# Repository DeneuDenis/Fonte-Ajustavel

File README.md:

# Fonte-Ajustavel
### Objetivo: montar uma fonte de tensão ajustável entre 12V e 3V que funcione com uma corrente de saída de 100 mA.
# Componentes
Todos os preços foram conferidos no site https://www.baudaeletronica.com.br
| Componente  |  Preço  |
| ------------------- | ------------------- |
|  Capacitor Eletrolítico 470uF / 35V |  R$ 0,77 |
|  Resistor 2K7 5% (1/4W) |  R$ 0,05 |
|  Resistor 1K8 5% (1/4W) |  R$ 0,05 |
|  Ponte Retificadora KBPC1010 |  R$ 3,67 |
|  Diodo Zener 1N4743 [13V / 1W] |  R$ 0,19 |
|  Potenciômetro Linear de 5K (5000Ω) |  R$ 1,99 |
|  Transistor NPN BC337 |  R$ 0,20 |
|  Transformador Trafo 12V+12V 500mA - 110/220VAC |  R$ 32,86 |
Vídeo curto com explicação dos valores escolhidos: https://drive.google.com/file/d/1bg3l0aVqp5aAvlKfoLDQY94b8t1-KplE/view?usp=sharing

## ponte retificadora
Aproveita a energia vinda do gerador(tomada) em ambas as fases da onda.
## diodo zenner
O regulador de tensão, corta a tensão abaixo do ripple do capacitor, permitindo uma tensão constante na carga.
## potenciometro
Permite regular a tensão a tensão na carga.
## capacitor
O capacitor armazena um pouco da energia de cada onda vinda do gerador de corrente alternada(no nosso caso, a tomada) e libera tal energia quando a tensão cinda da fonte é inferior à do capacitor, evitando grandes variaçõesd e tensão.
## transistor
Amplifica e barra a corrente no circuito.
## resistor
limita a passagem da corrente no circuito.
## transformador
Diminui a tensão vinda da tomada.
# Link para o Falstad
https://tinyurl.com/yhgow4pc
# Imagem do circuito

# Imagem do schematic

# Imagem do board

# Autoria 
Daniel Afonso Borges dos Santos- 12608581

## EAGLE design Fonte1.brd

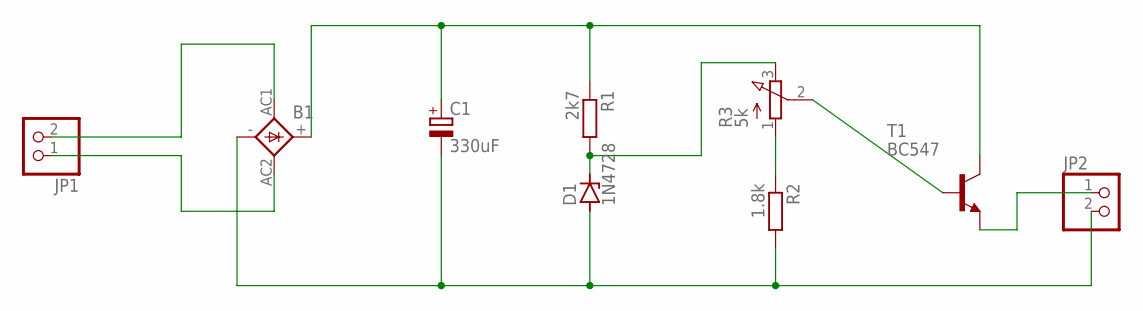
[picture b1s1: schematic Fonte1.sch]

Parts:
B1: 1KAB
C1: 330uF; E5-10,5
D1: 1N4728; DO41Z10
JP1, JP2: PINHD-1X2; 1X02
R1: 2k7; 0207/10
R2: 1.8k; 0207/10
R3: 5k; 3RP/1610N
T1: BC547; TO92

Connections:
unnamed: B1.AC1, JP1.2
unnamed: B1.AC2, JP1.1
unnamed: B1.+, C1.+, R1.1, T1.3 (C)
unnamed: D1.C, R1.2, R3.3 (E)
unnamed: B1.-, C1.-, D1.A, JP2.2, R2.2
unnamed: JP2.1, T1.1 (E)
unnamed: R3.2 (S), T1.2 (B)
unnamed: R2.1, R3.1 (A)

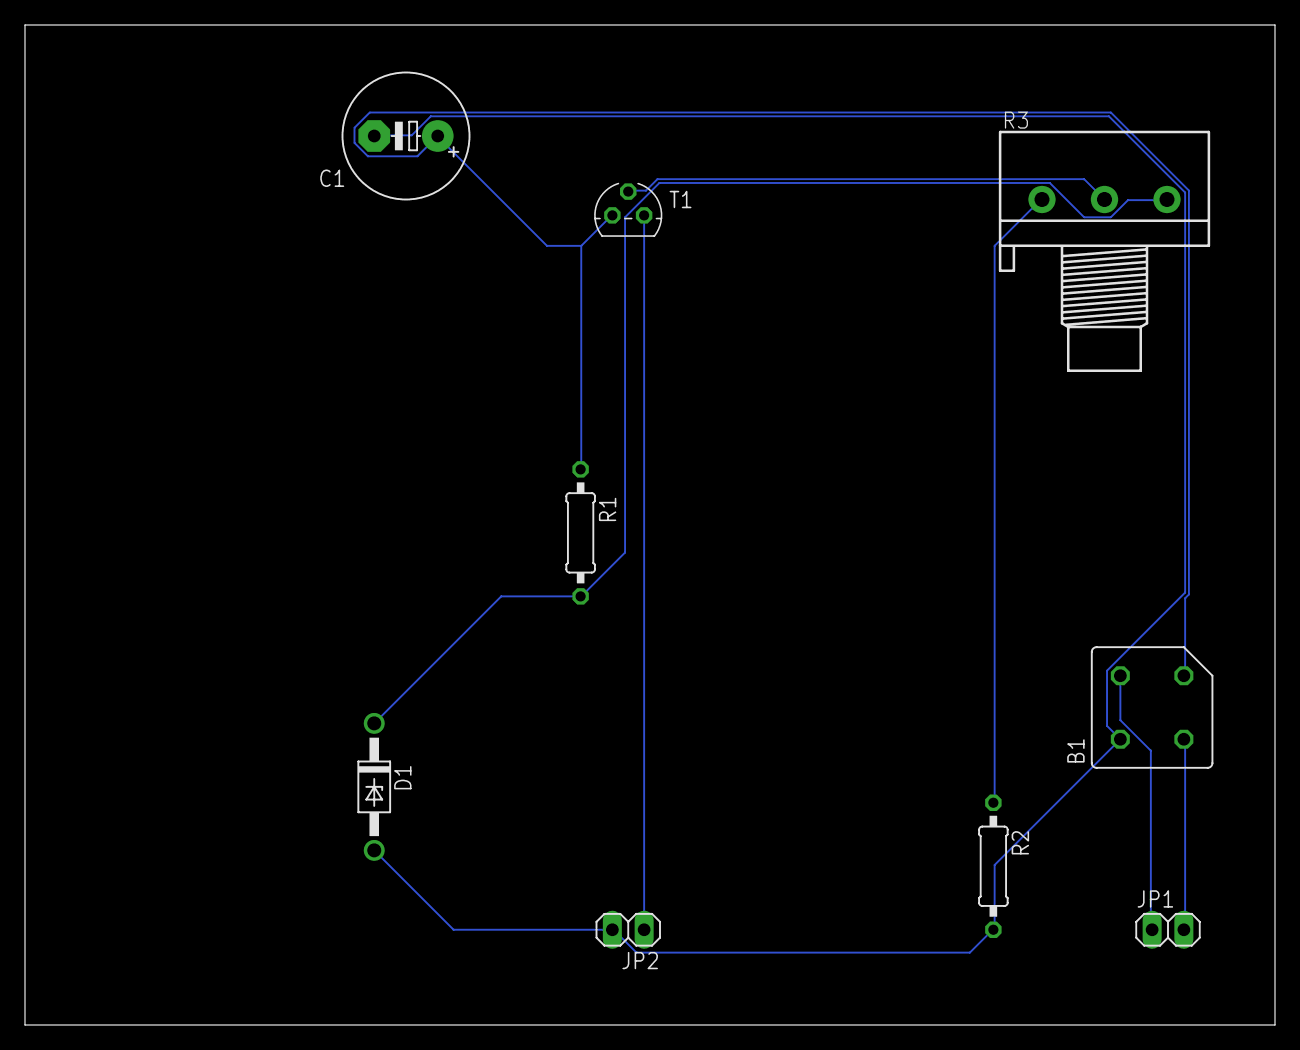
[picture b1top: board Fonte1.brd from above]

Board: 2 copper layers, 100.0 x 80.0 mm, 9 parts (0 on the bottom side), 8 nets.
